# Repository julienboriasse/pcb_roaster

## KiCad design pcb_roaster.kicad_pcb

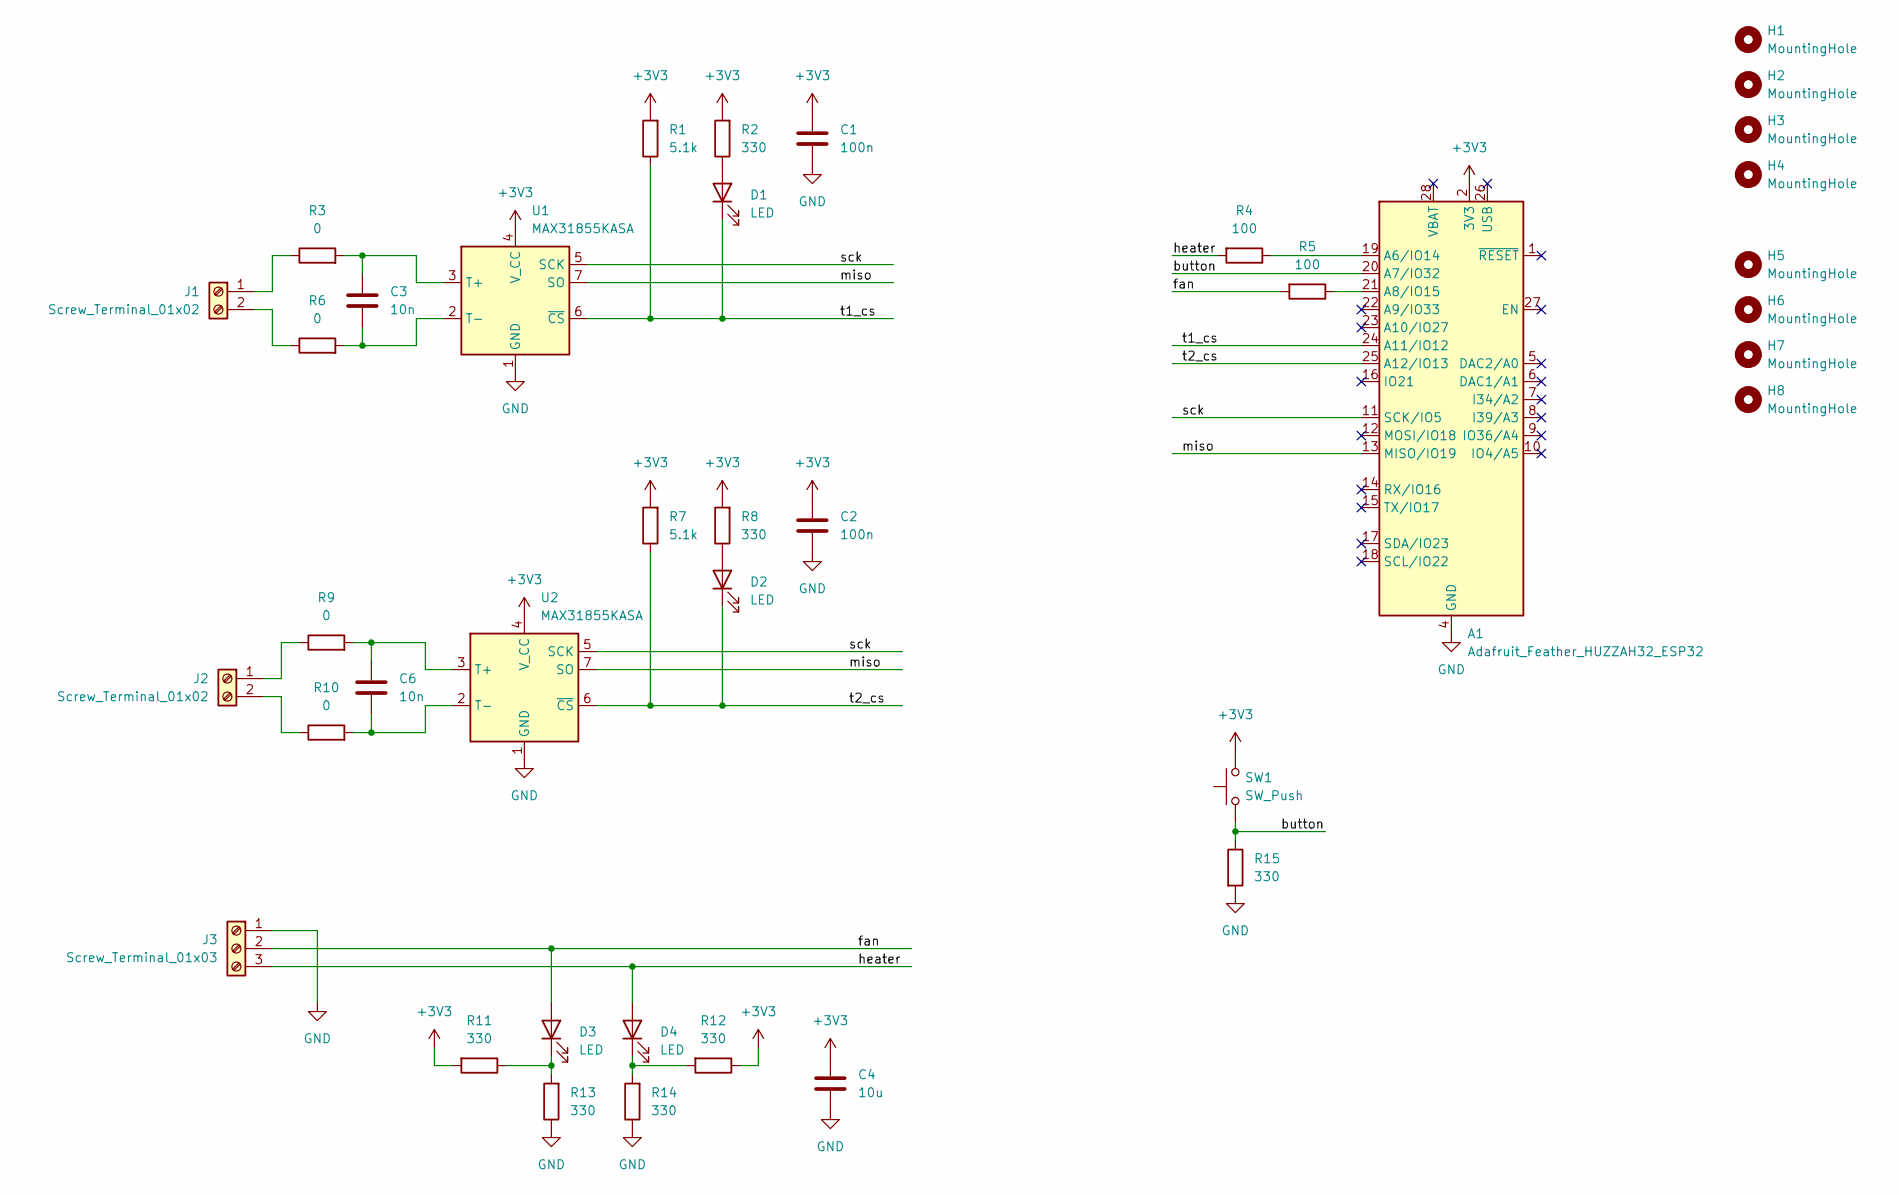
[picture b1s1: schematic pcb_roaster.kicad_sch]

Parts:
A1: Adafruit_Feather_HUZZAH32_ESP32; Adafruit_Feather
C1, C2: 100n; C_0805_2012Metric_Pad1.18x1.45mm_HandSolder
C3, C6: 10n; C_0805_2012Metric_Pad1.18x1.45mm_HandSolder
C4: 10u; C_0805_2012Metric_Pad1.18x1.45mm_HandSolder
D1, D2, D3, D4: LED; LED_0805_2012Metric_Pad1.15x1.40mm_HandSolder
H1, H2, H3, H4: MountingHole; MountingHole_2.5mm
H5, H6, H7, H8: MountingHole; MountingHole_3.2mm_M3
J1, J2: Screw_Terminal_01x02; TerminalBlock_TE_282834-2_1x02_P2.54mm_Horizontal
J3: Screw_Terminal_01x03; TerminalBlock_TE_282834-3_1x03_P2.54mm_Horizontal
R1, R7: 5.1k; R_0805_2012Metric_Pad1.20x1.40mm_HandSolder
R2, R8, R11, R12, R13, R14, R15: 330; R_0805_2012Metric_Pad1.20x1.40mm_HandSolder
R3, R6, R9, R10: 0; R_0805_2012Metric_Pad1.20x1.40mm_HandSolder
R4, R5: 100; R_0805_2012Metric_Pad1.20x1.40mm_HandSolder
SW1: SW_Push; SW_SPST_B3S-1000
U1, U2: MAX31855KASA; SOIC-8_3.9x4.9mm_P1.27mm

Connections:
+3V3: A1.2 (3V3), C1.1, C2.1, C4.1, R1.2, R2.2, R7.2, R8.2, R11.2, R12.1, SW1.2, U1.4 (V_CC), U2.4 (V_CC)
/button: A1.20 (A7/IO32), R15.1, SW1.1
/fan: D3.2 (A), J3.2, R5.2
/heater: D4.2 (A), J3.3, R4.2
/miso: A1.13 (MISO/IO19), U1.7 (SO), U2.7 (SO)
/sck: A1.11 (SCK/IO5), U1.5 (SCK), U2.5 (SCK)
/t1_cs: A1.24 (A11/IO12), D1.1 (K), R1.1, U1.6 (~CS)
/t2_cs: A1.25 (A12/IO13), D2.1 (K), R7.1, U2.6 (~CS)
GND: A1.4 (GND), C1.2, C2.2, C4.2, J3.1, R13.1, R14.1, R15.2, U1.1 (GND), U2.1 (GND)
unnamed: A1.19 (A6/IO14), R4.1
unnamed: A1.21 (A8/IO15), R5.1
unnamed: D1.2 (A), R2.1
unnamed: D2.2 (A), R8.1
unnamed: D3.1 (K), R11.1, R13.2
unnamed: D4.1 (K), R12.2, R14.2
unnamed: J1.1, R3.1
unnamed: J1.2, R6.1
unnamed: J2.1, R9.1
unnamed: J2.2, R10.1
unnamed: C3.1, R3.2, U1.3 (T+)
unnamed: C3.2, R6.2, U1.2 (T-)
unnamed: C6.1, R9.2, U2.3 (T+)
unnamed: C6.2, R10.2, U2.2 (T-)

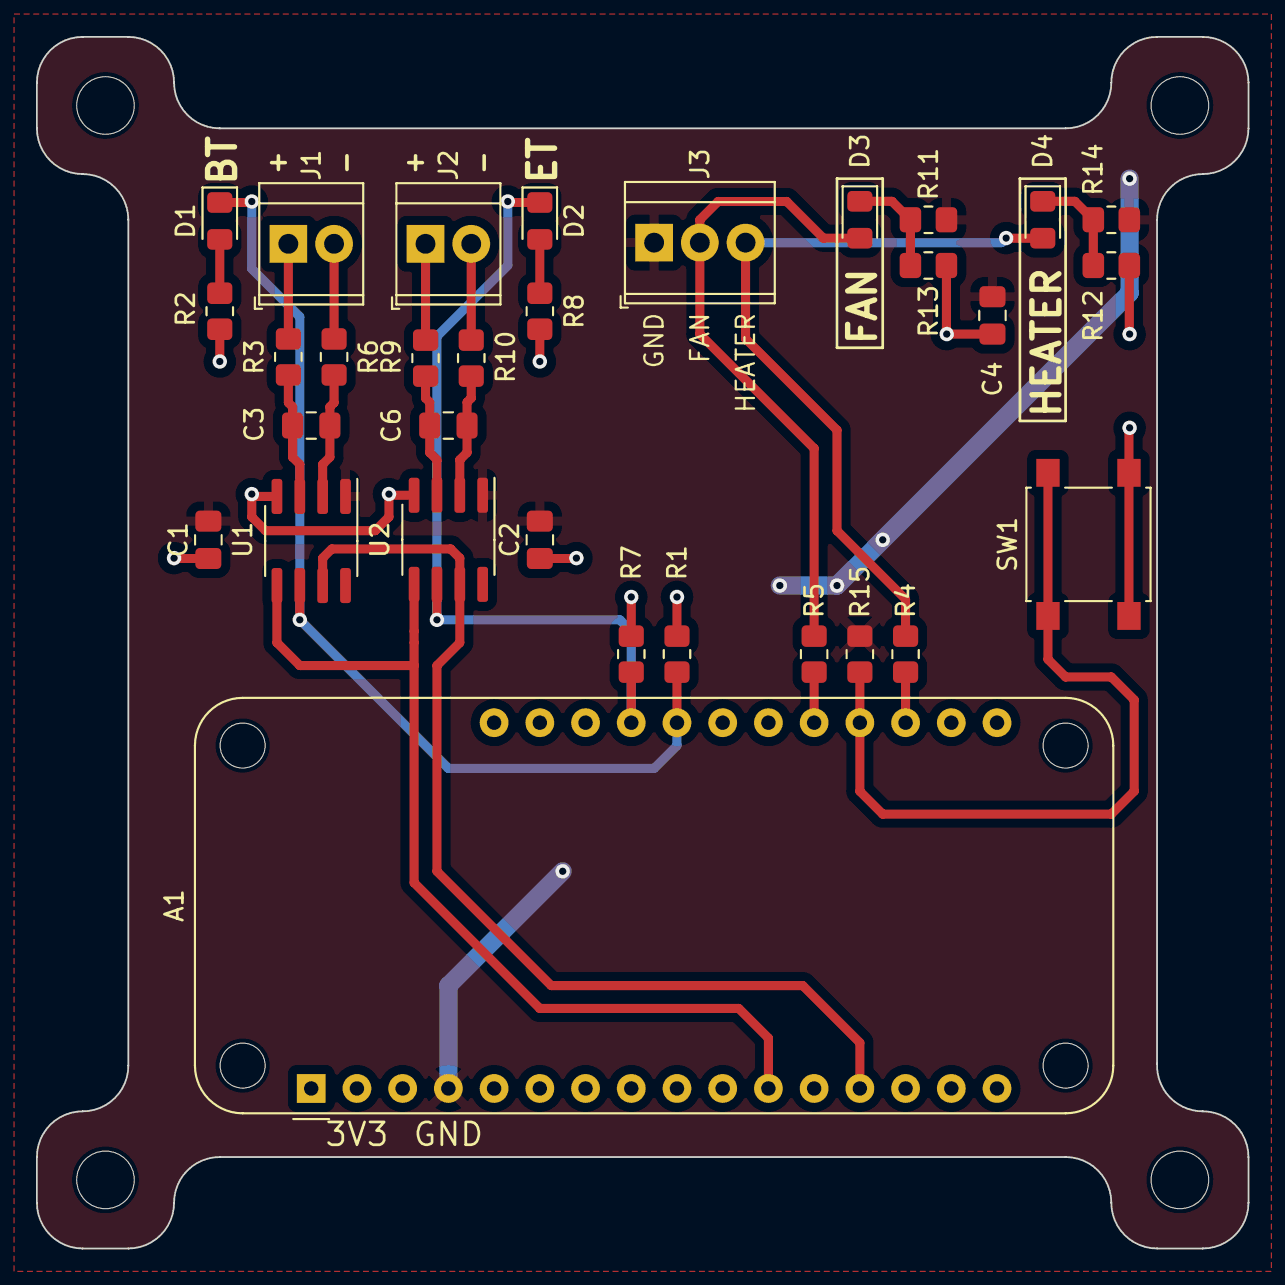
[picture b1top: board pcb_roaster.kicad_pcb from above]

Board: 2 copper layers, 67.3 x 67.3 mm, 39 parts (0 on the bottom side), 23 nets.

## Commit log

2024-01-30 New project
2024-01-30 Add 3D models
2024-01-30 Update PCB
2024-01-30 Add image
2024-01-31 Clear DRC issues
